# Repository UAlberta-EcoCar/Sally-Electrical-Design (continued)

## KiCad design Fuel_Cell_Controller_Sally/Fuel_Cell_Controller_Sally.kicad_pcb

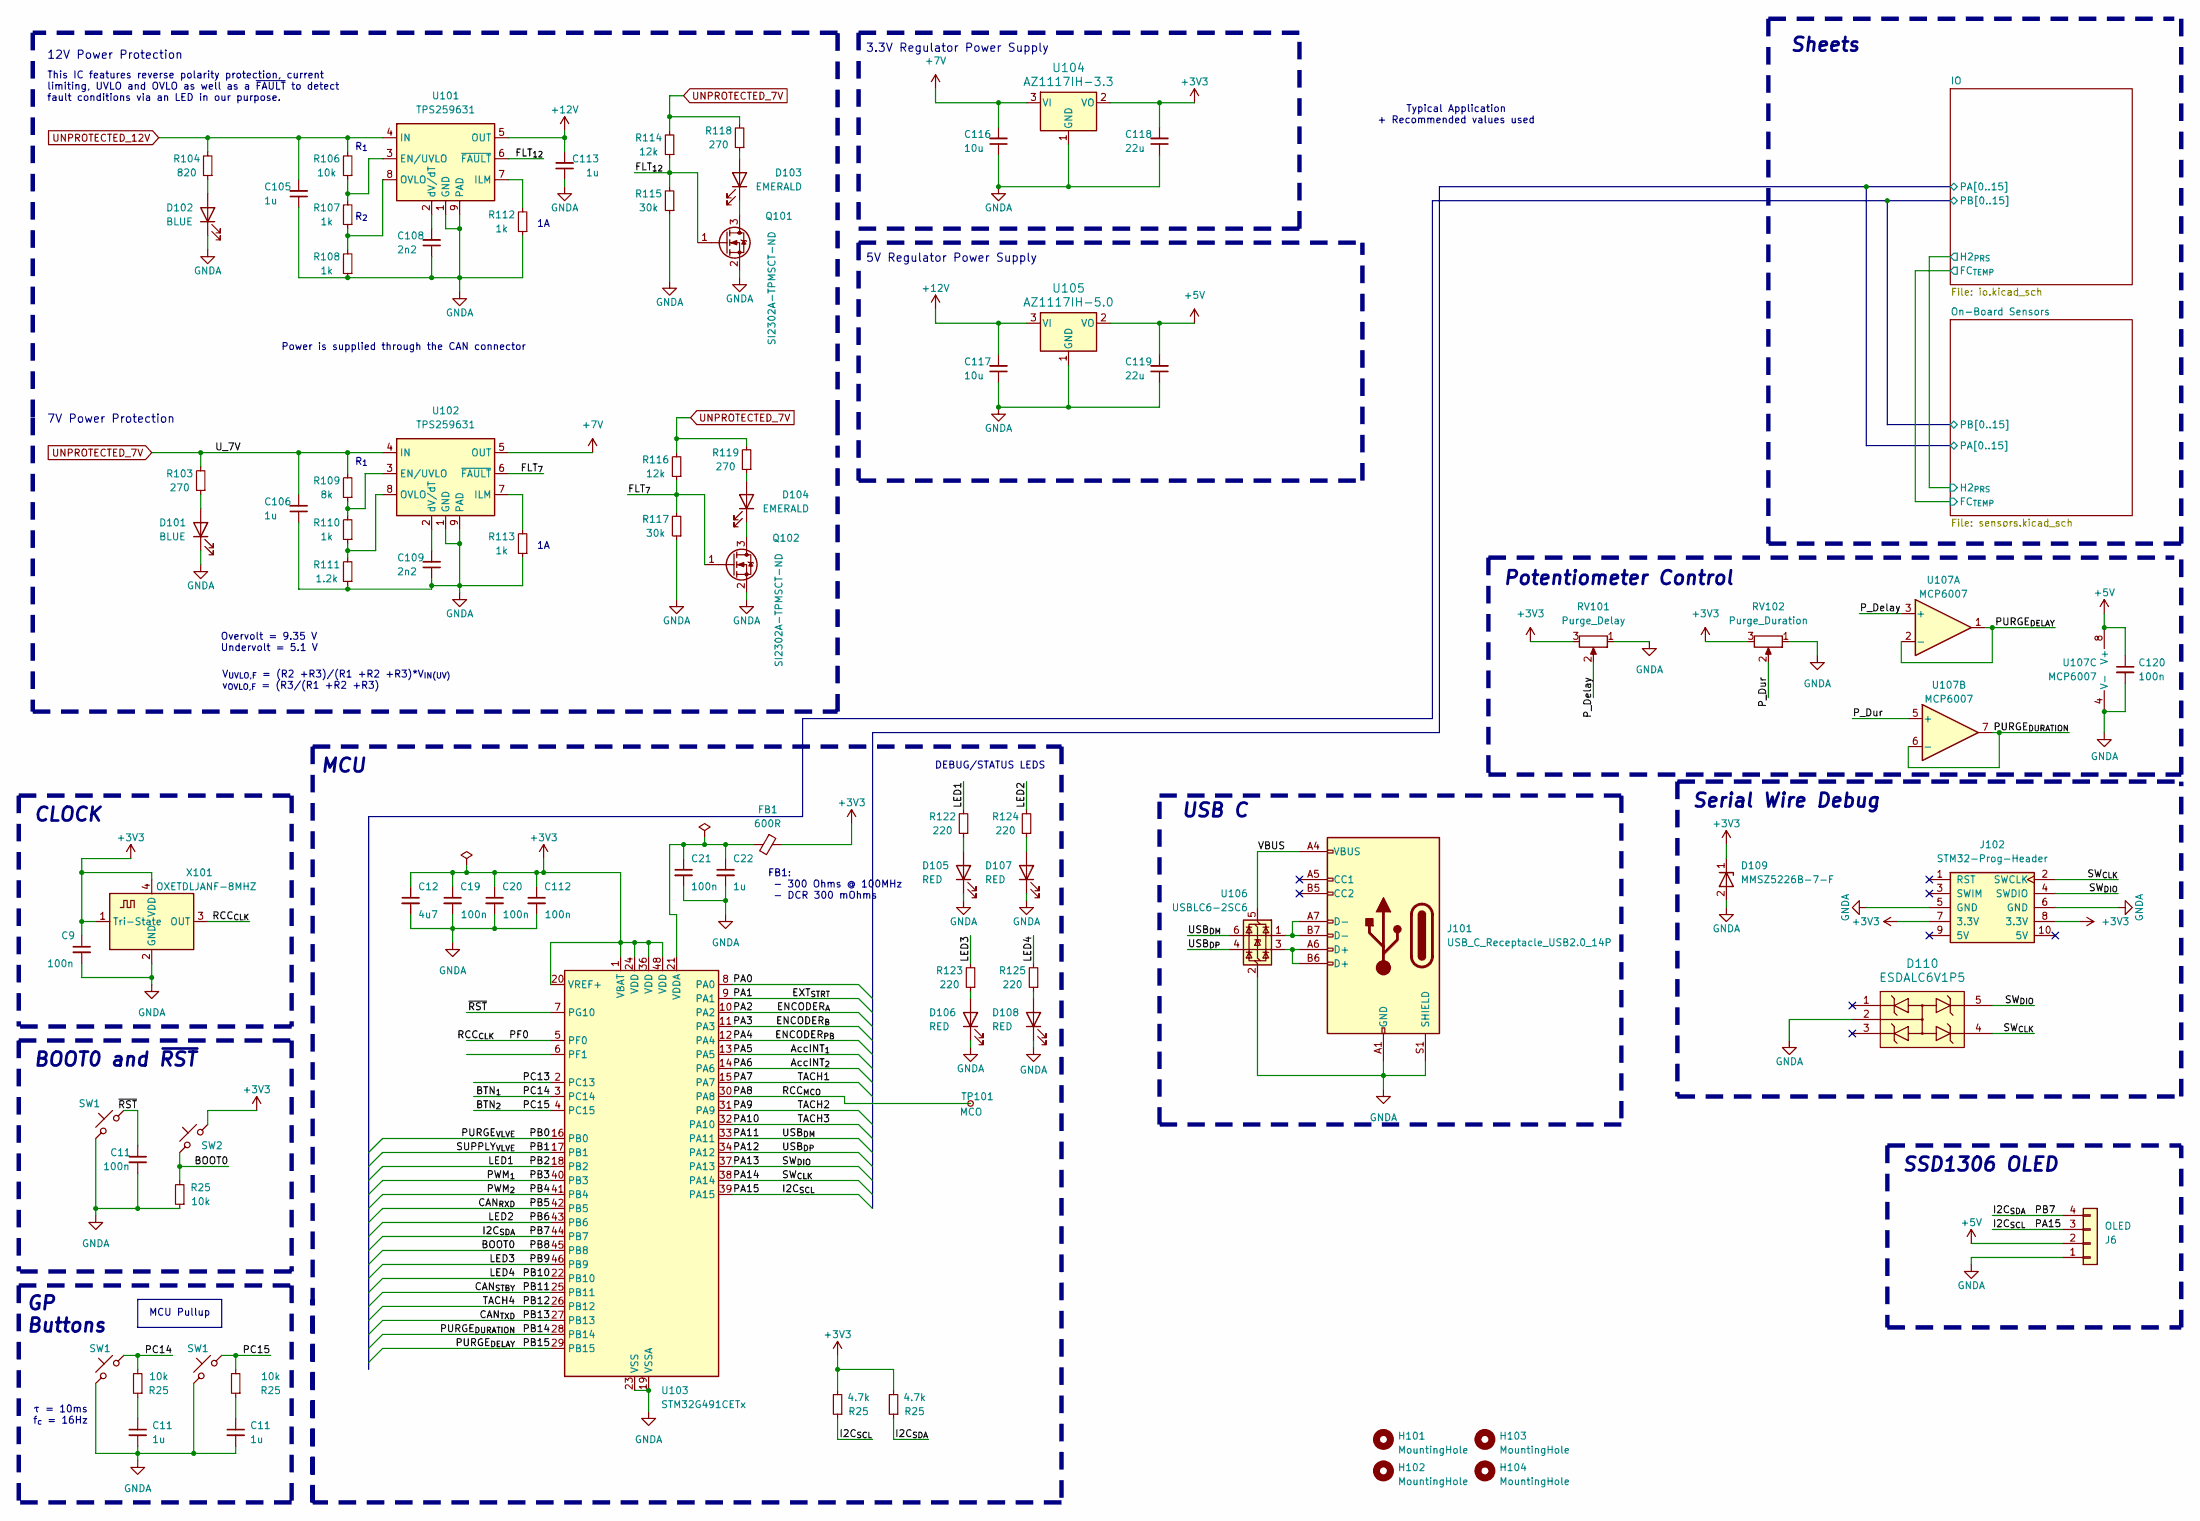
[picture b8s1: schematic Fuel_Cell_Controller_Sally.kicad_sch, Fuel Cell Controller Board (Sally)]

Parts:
C9, C120: 100n; C_0603_1608Metric; Part# C14663
C11: 1u; C_0603_1608Metric; Part# C23630
C12: 4u7; C_0603_1608Metric; Part# C19666
C19, C20, C21, C112: 100n; C_0603_1608Metric; Part# C1525
C22, C105, C106, C113: 1u; C_0603_1608Metric; Part# C15849
C108, C109: 2n2; C_0603_1608Metric; Part# C1604
C116, C117: 10u; C_0603_1608Metric; Part# C15849
C118, C119: 22u; C_0603_1608Metric; Part# C15849
D101, D102: BLUE; LED_0603_1608Metric; Part# C72041
D103, D104: EMERALD; LED_0603_1608Metric; Part# C72043
D105, D106, D107, D108: RED; LED_0603_1608Metric; Part# C72041
D109: MMSZ5226B-7-F; D_SOD_123_M; Part# C155250
D110: ESDALC6V1P5
FB1: 600R; L_0805_2012Metric; Part# C1017
H101, H102, H103, H104: MountingHole; MountingHole_3.5mm
J6: OLED; Display_128x64_096_I2C; Part# N/A
J101: USB_C_Receptacle_USB2.0_14P; USB_C_Receptacle_GCT_USB4105-xx-A_16P_TopMnt_Horizontal
J102: STM32-Prog-Header; IDC-STM32-Prog-Header_2x05_P2.54mm_Vertical
Q101, Q102: SI2302A-TPMSCT-ND; SOT-23-3; Part# SI2302A-TPMSCT-ND
R25: 4.7k; R_0603_1608Metric; Part# C23162
R103, R118, R119: 270; R_0603_1608Metric; Part# C22966
R104: 820; R_0603_1608Metric; Part# C23253
R106: 10k; R_0603_1608Metric; Part# C25804
R107, R108: 1k; R_0603_1608Metric; Part# C3013565
R109: 8k; R_0603_1608Metric; Part# C25950
R110: 1k; R_0603_1608Metric; Part# C25950
R111: 1.2k; R_0603_1608Metric; Part# C25950
R112, R113: 1k; R_0603_1608Metric; Part# C21190
R114, R116: 12k; R_0603_1608Metric; Part# C25803
R115, R117: 30k; R_0603_1608Metric; Part# C25803
R122, R123, R124, R125: 220; R_0603_1608Metric; Part# C22966
RV101: Purge_Delay; Potentiometer_Bourns_PTV09A-1_Single_Vertical
RV102: Purge_Duration; Potentiometer_Bourns_PTV09A-1_Single_Vertical
SW1: SW_PUSH_6mm_H5mm; Part# N/A
SW2: PTS815 SJM 250 SMTR LFS; SW_PUSH_6mm_H5mm; Part# C2689510
TP101: MCO; TestPoint_Pad_D1.0mm; Part# N/A
U101, U102: TPS259631; TI_SO-PowerPAD-8
U103: STM32G491CETx; LQFP-48_7x7mm_P0.5mm
U104: AZ1117IH-3.3; SOT-223-3_TabPin2
U105: AZ1117IH-5.0; SOT-223-3_TabPin2
U106: USBLC6-2SC6; SOT-23-6
U107: MCP6007; SOIC-8_3.9x4.9mm_P1.27mm
X101: OXETDLJANF-8MHZ; Crystal_SMD_3225-4Pin_3.2x2.5mm

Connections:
+3V3: C112.1, C118.2, D109.1, J102.7 (3.3V), J102.8 (3.3V), RV101.3, RV102.3, U103.1 (VBAT), U103.20 (VREF+), U103.24 (VDD), U103.36 (VDD), U103.48 (VDD), U104.2 (VO), X101.1 (Tri-State), X101.4 (VDD); also elsewhere on the board
+5V: C119.2, C120.1, U105.2 (VO), U107.8 (V+); also elsewhere on the board
+7V: C116.2, U102.5 (OUT), U104.3 (VI)
+12V: C113.2, C117.2, U101.5 (OUT), U105.3 (VI); also elsewhere on the board
/BTN_{1}: U103.3 (PC14); also elsewhere on the board
/BTN_{2}: U103.4 (PC15); also elsewhere on the board
/FLT_{7}: Q102.1 (G), R116.1, R117.2, U102.6 (~FAULT)
/FLT_{12}: Q101.1 (G), R114.1, R115.2, U101.6 (~FAULT)
/IO /PA0: U103.8 (PA0)
/IO /PA1: U103.9 (PA1); also elsewhere on the board
/IO /PA2: U103.10 (PA2); also elsewhere on the board
/IO /PA3: U103.11 (PA3); also elsewhere on the board
/IO /PA4: U103.12 (PA4); also elsewhere on the board
/IO /PA5: U103.13 (PA5); also elsewhere on the board
/IO /PA6: U103.14 (PA6); also elsewhere on the board
/IO /PA7: U103.15 (PA7); also elsewhere on the board
/IO /PA8: TP101.1, U103.30 (PA8)
/IO /PA9: U103.31 (PA9); also elsewhere on the board
/IO /PA10: U103.32 (PA10); also elsewhere on the board
/IO /PA11: U103.33 (PA11), U106.6 (I/O1)
/IO /PA12: U103.34 (PA12), U106.4 (I/O2)
/IO /PA13: D110.5, J102.4 (SWDIO), U103.37 (PA13)
/IO /PA14: D110.4, J102.2 (SWCLK), U103.38 (PA14)
/IO /PA15: U103.39 (PA15); also elsewhere on the board
/IO /PB0: U103.16 (PB0); also elsewhere on the board
/IO /PB1: U103.17 (PB1); also elsewhere on the board
/IO /PB2: R122.2, U103.18 (PB2)
/IO /PB3: U103.40 (PB3); also elsewhere on the board
/IO /PB4: U103.41 (PB4); also elsewhere on the board
/IO /PB5: U103.42 (PB5); also elsewhere on the board
/IO /PB6: R124.2, U103.43 (PB6)
/IO /PB7: U103.44 (PB7); also elsewhere on the board
/IO /PB8: U103.45 (PB8); also elsewhere on the board
/IO /PB9: R123.2, U103.46 (PB9)
/IO /PB10: R125.2, U103.22 (PB10)
/IO /PB11: U103.25 (PB11); also elsewhere on the board
/IO /PB12: U103.26 (PB12); also elsewhere on the board
/IO /PB13: U103.27 (PB13); also elsewhere on the board
/IO /PB14: U103.28 (PB14), U107.6 (-), U107.7
/IO /PB15: U103.29 (PB15), U107.1, U107.2 (-)
/PC13: U103.2 (PC13)
/PF0: U103.5 (PF0), X101.3 (OUT)
/P_Delay: RV101.2, U107.3 (+)
/P_Dur: RV102.2, U107.5 (+)
/VBUS: J101.A4 (VBUS), J101.A9 (VBUS), J101.B4 (VBUS), J101.B9 (VBUS), U106.5 (VBUS)
/~RST: U103.7 (PG10); also elsewhere on the board
GNDA: C105.1, C106.1, C108.1, C109.1, C112.2, C113.1, C116.1, C117.1, C118.1, C119.1, C120.2, D101.1 (K), D102.1 (K), D105.1 (K), D106.1 (K), D107.1 (K), D108.1 (K), D109.2, D110.2, J101.A1 (GND), J101.A12 (GND), J101.B1 (GND), J101.B12 (GND), J101.S1 (SHIELD), J102.5 (GND), J102.6 (GND), Q101.2 (S), Q102.2 (S), R108.1, R111.1, R112.1, R113.1, R115.1, R117.1, RV101.1, RV102.1, U101.1 (GND), U101.9 (PAD), U102.1 (GND), U102.9 (PAD), U103.19 (VSSA), U103.23 (VSS), U103.35 (VSS), U103.47 (VSS), U104.1 (GND), U105.1 (GND), U106.2 (GND), U107.4 (V-), X101.2 (GND); also elsewhere on the board
unnamed: D101.2 (A), R103.1
unnamed: D102.2 (A), R104.1
unnamed: D103.2 (A), R118.1
unnamed: D103.1 (K), Q101.3 (D)
unnamed: D104.2 (A), R119.1
unnamed: D104.1 (K), Q102.3 (D)
unnamed: D105.2 (A), R122.1
unnamed: D106.2 (A), R123.1
unnamed: D107.2 (A), R124.1
unnamed: D108.2 (A), R125.1
unnamed: J101.A6 (D+), J101.B6 (D+), U106.3 (I/O2)
unnamed: J101.A7 (D-), J101.B7 (D-), U106.1 (I/O1)
unnamed: R106.1, R107.2, U101.3 (EN/UVLO)
unnamed: R112.2, U101.7 (ILM)
unnamed: R107.1, R108.2, U101.8 (OVLO)
unnamed: C108.2, U101.2 (dV/dT)
unnamed: R109.1, R110.2, U102.3 (EN/UVLO)
unnamed: R113.2, U102.7 (ILM)
unnamed: R110.1, R111.2, U102.8 (OVLO)
unnamed: C109.2, U102.2 (dV/dT)
unnamed 95: U103.21 (VDDA); also elsewhere on the board
UNPROTECTED_7V: C106.2, R103.2, R109.2, R114.2, R116.2, R118.2, R119.2, U102.4 (IN); also elsewhere on the board
UNPROTECTED_12V: C105.2, R104.2, R106.2, U101.4 (IN); also elsewhere on the board

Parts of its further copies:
C101: 100n; C_0603_1608Metric; Part# C14663
C103, C104: 1u; C_0603_1608Metric; Part# C23630
C107: 4u7; C_0603_1608Metric; Part# C19666
C110, C111, C114: 100n; C_0603_1608Metric; Part# C1525
C115: 1u; C_0603_1608Metric; Part# C15849
FB101: 600R; L_0805_2012Metric; Part# C1017
J103: OLED; Display_128x64_096_I2C; Part# N/A
R120, R121: 4.7k; R_0603_1608Metric; Part# C23162
SW102, SW104: SW_PUSH_6mm_H5mm; Part# N/A
SW103: PTS815 SJM 250 SMTR LFS; SW_PUSH_6mm_H5mm; Part# C2689510

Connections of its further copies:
+3V3: C101.1, C107.1, C110.1, C111.1, FB101.1, R120.2, R121.2, SW103.2; also elsewhere on the board
+5V: J103.2; also elsewhere on the board
/BTN_{1}: SW102.2; also elsewhere on the board
/BTN_{2}: SW104.2; also elsewhere on the board
/IO /PA15: J103.3, R120.1; also elsewhere on the board
/IO /PB7: J103.4, R121.1; also elsewhere on the board
/IO /PB8: SW103.1; also elsewhere on the board
GNDA: C101.2, C103.2, C104.2, C107.2, C110.2, C111.2, C114.2, C115.2, J103.1, SW102.1, SW104.1; also elsewhere on the board
unnamed 61: C103.1; also elsewhere on the board
unnamed 62: C104.1; also elsewhere on the board
unnamed 95: C114.1, C115.1, FB101.2; also elsewhere on the board

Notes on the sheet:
MCU
R_{1}
FB1: - 300 Ohms @ 100MHz - DCR 300 mOhms
Sheets
12V Power Protection
Power is supplied through the CAN connector
Potentiometer Control
5V Regulator Power Supply
DEBUG/STATUS LEDS
CLOCK
Typical Application + Recommended values used
GP Buttons
SSD1306 OLED
This IC features reverse polarity protection, current limiting, UVLO and OVLO as well as a ~{FAULT} to detect fault conditions via an LED in our purpose.
7V Power Protection
R_{2}
3.3V Regulator Power Supply
USB C
Serial Wire Debug
BOOT0 and ~{RST}
Overvolt = 9.35 V Undervolt = 5.1 V
MCU Pullup
τ = 10ms f_{c} = 16Hz
V_{UVLO,F} = (R2 +R3)/(R1 +R2 +R3)*V_{IN(UV)} v_{OVLO,F} = (R3/(R1 +R2 +R3)

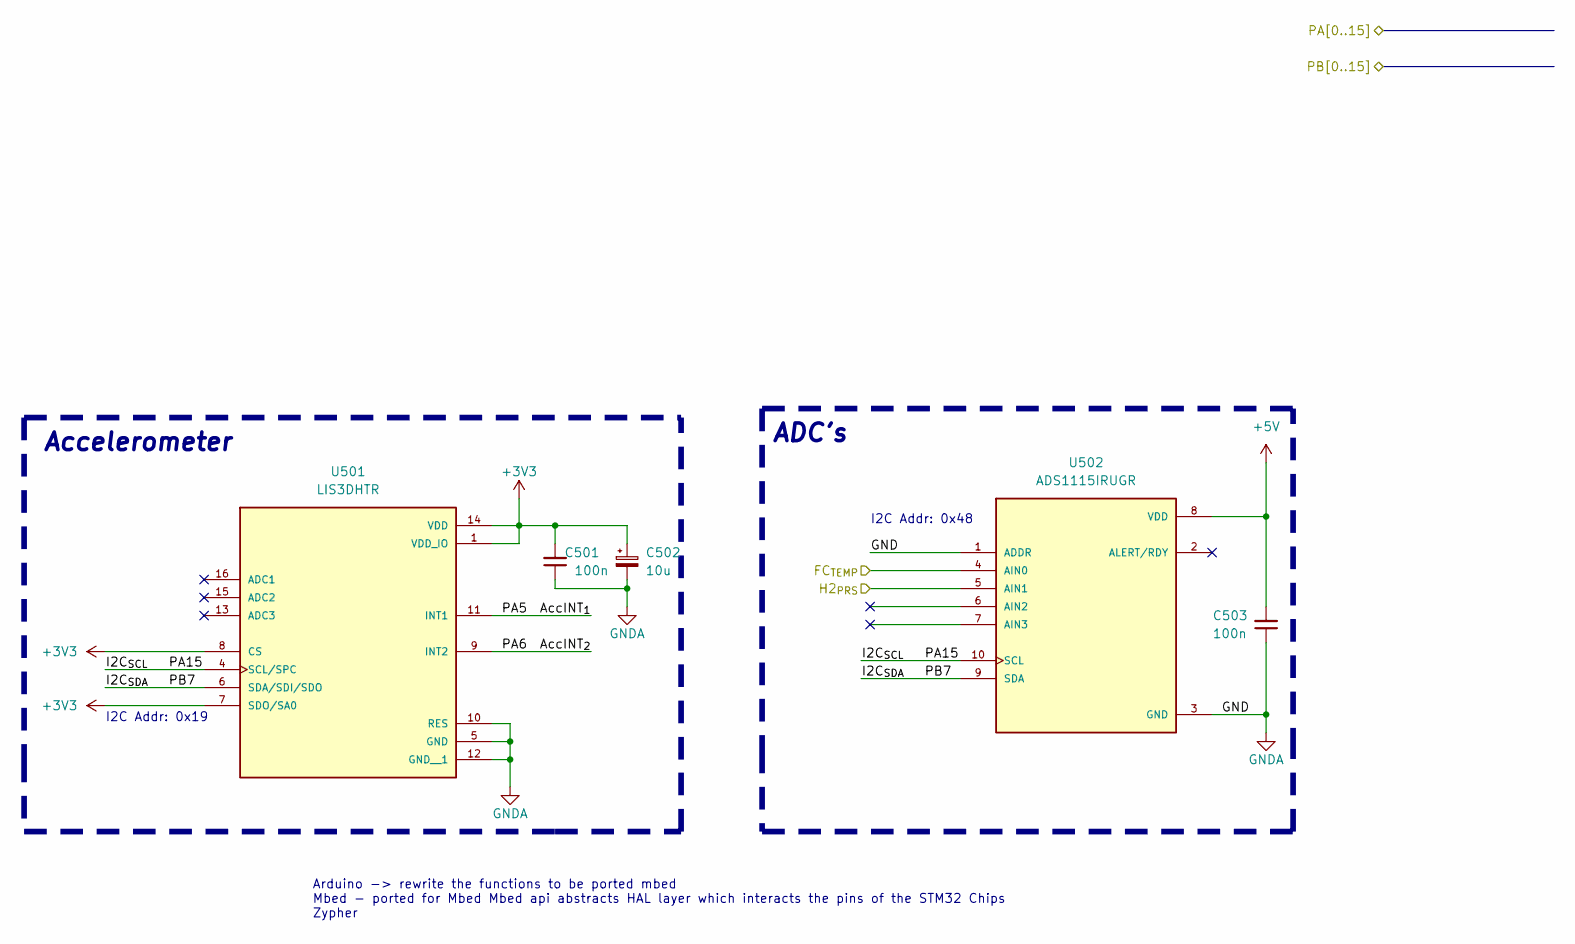
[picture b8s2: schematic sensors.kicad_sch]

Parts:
C501, C503: 100n; C_0603_1608Metric; Part# C14663
C502: 10u; CP_Elec_3x5.3
U501: LIS3DHTR; XDCR_LIS3DHTR
U502: ADS1115IRUGR; IC_ADS1115IRUGR

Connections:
+3V3: C501.2, C502.1, U501.1 (VDD_IO), U501.7 (SDO/SA0), U501.8 (CS), U501.14 (VDD); also elsewhere on the board
+5V: C503.2, U502.8 (VDD); also elsewhere on the board
/IO /FC_{TEMP}: U502.4 (AIN0); also elsewhere on the board
/IO /H2_{PRS}: U502.5 (AIN1); also elsewhere on the board
/IO /PA5: U501.11 (INT1); also elsewhere on the board
/IO /PA6: U501.9 (INT2); also elsewhere on the board
/IO /PA15: U501.4 (SCL/SPC), U502.10 (SCL); also elsewhere on the board
/IO /PB7: U501.6 (SDA/SDI/SDO), U502.9 (SDA); also elsewhere on the board
GNDA: C501.1, C502.2, C503.1, U501.5 (GND), U501.10 (RES), U501.12 (GND__1), U502.1 (ADDR), U502.3 (GND); also elsewhere on the board

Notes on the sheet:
I2C Addr: 0x48
Arduino -> rewrite the functions to be ported mbed Mbed - ported for Mbed Mbed api abstracts HAL layer which interacts the pins of the STM32 Chips Zypher
ADC's
I2C Addr: 0x19
Accelerometer

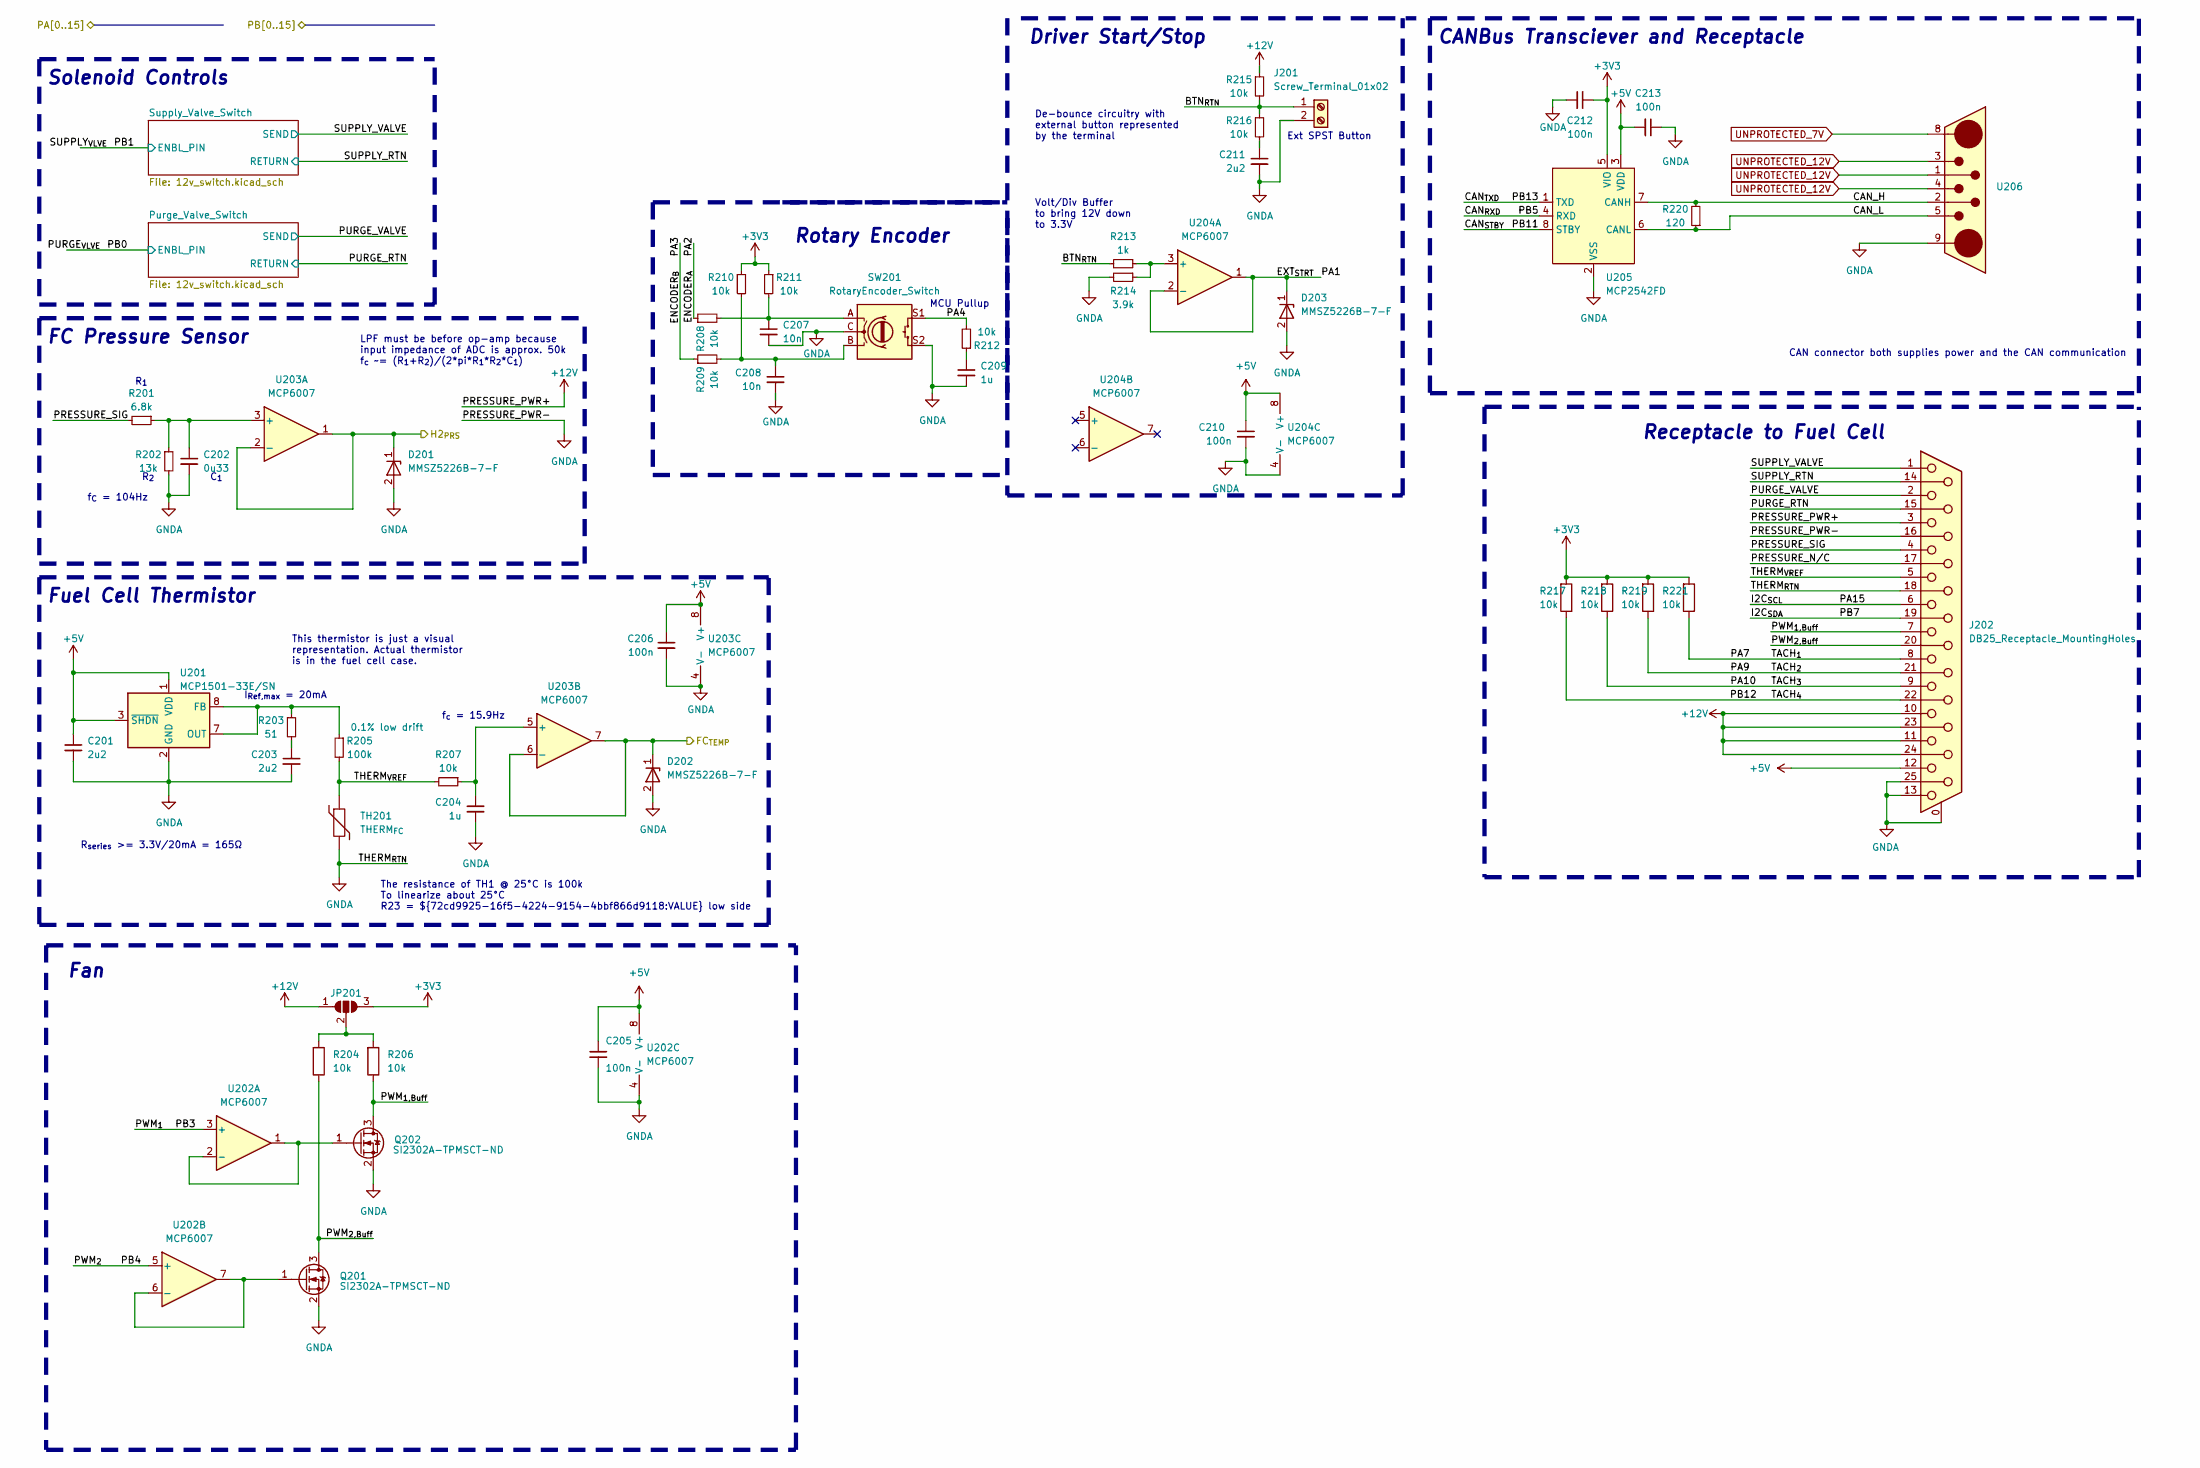
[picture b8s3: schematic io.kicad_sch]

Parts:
C201, C203, C211: 2u2; C_0603_1608Metric; Part# C23630
C202: 0u33; C_0603_1608Metric; Part# C1615
C204: 1u; C_0603_1608Metric; Part# C15849
C205: 100n; C_0603_1608Metric; Part# C77049
C206, C210, C212, C213: 100n; C_0603_1608Metric; Part# C14663
C207, C208: 10n; C_0603_1608Metric; Part# C23630
C209: 1u; C_0603_1608Metric; Part# C23630
D201, D202, D203: MMSZ5226B-7-F; D_SOD_123_M; Part# C155250
J201: Screw_Terminal_01x02; TerminalBlock_Phoenix_MKDS-1,5-2-5.08_1x02_P5.08mm_Horizont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; Part# 277-1247-ND
J202: DB25_Receptacle_MountingHoles; DSUB-25_Female_Horizontal_P2.77x2.84mm_EdgePinOffset9.90mm_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
JP201: SolderJumper_3_Open; SolderJumper-3_P1.3mm_Open_RoundedPad1.0x1.5mm_NumberLabels
Q201, Q202: SI2302A-TPMSCT-ND; SOT-23-3; Part# SI2302A-TPMSCT-ND
R201: 6.8k; R_0603_1608Metric; Part# C23212
R202: 13k; R_0603_1608Metric; Part# C22797
R203: 51; R_0603_1608Metric; Part# C23197
R204, R206, R217, R218, R219, R221: 10k; R_0603_1608Metric; LCSC # C25804
R205: 100k; R_0603_1608Metric; Part# C25803
R207, R208, R209, R210, R211, R212, R215, R216: 10k; R_0603_1608Metric; Part# C25804
R213: 1k; R_0603_1608Metric; Part# C4190
R214: 3.9k; R_0603_1608Metric; Part# C23253
R220: 120; R_0603_1608Metric; Part# C22787
SW201: RotaryEncoder_Switch; RotaryEncoder_Bourns_Vertical_PEC12R-3x17F-Sxxxx
TH201: THERM_{FC}; Part# N/A
U201: MCP1501-33E/SN; SOIC-8_3.9x4.9mm_P1.27mm; Part# MCP1501-33E/SN-ND
U202, U203, U204: MCP6007; SOIC-8_3.9x4.9mm_P1.27mm
U205: MCP2542FD; SOIC-8_3.9x4.9mm_P1.27mm
U206: DB7W2-Male

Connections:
+3V3: C212.1, JP201.3 (B), R210.1, R211.1, R217.2, R218.2, R219.2, R221.2, U205.5 (VIO); also elsewhere on the board
+5V: C201.1, C205.1, C206.1, C210.1, C213.2, J202.12, U201.1 (VDD), U201.3 (~SHDN), U202.8 (V+), U203.8 (V+), U204.8 (V+), U205.3 (VDD); also elsewhere on the board
+12V: J202.1, J202.2, J202.3, J202.10, J202.11, J202.23, J202.24, JP201.1 (A), R215.1; also elsewhere on the board
/IO /BTN_{RTN}: J201.1, R213.2, R215.2, R216.1
/IO /CAN_H: R220.2, U205.7 (CANH), U206.2
/IO /CAN_L: R220.1, U205.6 (CANL), U206.5
/IO /FC_{TEMP}: D202.1, U203.6 (-), U203.7; also elsewhere on the board
/IO /H2_{PRS}: D201.1, U203.1, U203.2 (-); also elsewhere on the board
/IO /PA1: D203.1, U204.1, U204.2 (-); also elsewhere on the board
/IO /PA2: R208.1; also elsewhere on the board
/IO /PA3: R209.1; also elsewhere on the board
/IO /PA4: R212.2, SW201.S1; also elsewhere on the board
/IO /PA7: J202.8, R221.1; also elsewhere on the board
/IO /PA9: J202.21, R219.1; also elsewhere on the board
/IO /PA10: J202.9, R218.1; also elsewhere on the board
/IO /PA15: J202.6; also elsewhere on the board
/IO /PB3: U202.3 (+); also elsewhere on the board
/IO /PB4: U202.5 (+); also elsewhere on the board
/IO /PB5: U205.4 (RXD); also elsewhere on the board
/IO /PB7: J202.19; also elsewhere on the board
/IO /PB11: U205.8 (STBY); also elsewhere on the board
/IO /PB12: J202.22, R217.1; also elsewhere on the board
/IO /PB13: U205.1 (TXD); also elsewhere on the board
/IO /PRESSURE_N/C: J202.17
/IO /PRESSURE_SIG: J202.4, R201.2
/IO /PURGE_RTN: J202.15; also elsewhere on the board
/IO /PWM_{1,Buff}: J202.7, Q202.3 (D), R206.1
/IO /PWM_{2,Buff}: J202.20, Q201.3 (D), R204.1
/IO /SUPPLY_RTN: J202.14; also elsewhere on the board
/IO /THERM_{VREF}: J202.5, R205.2, R207.2, TH201.1
GNDA: C201.2, C202.2, C203.2, C204.2, C205.2, C206.2, C207.2, C208.2, C209.2, C210.2, C211.2, C212.2, C213.1, D201.2, D202.2, D203.2, J201.2, J202.0 (PAD), J202.13, J202.16, J202.18, J202.25, Q201.2 (S), Q202.2 (S), R202.2, R214.2, SW201.C, SW201.S2, TH201.2, U201.2 (GND), U201.4 (GND), U201.5 (GND), U201.6 (GND), U202.4 (V-), U203.4 (V-), U204.4 (V-), U205.2 (VSS), U206.9; also elsewhere on the board
unnamed: C203.1, R203.2
unnamed: C207.1, R208.2, R211.2, SW201.A
unnamed: C208.1, R209.2, R210.2, SW201.B
unnamed: C209.1, R212.1
unnamed: C211.1, R216.2
unnamed: JP201.2 (C), R204.2, R206.2
unnamed: Q201.1 (G), U202.6 (-), U202.7
unnamed: Q202.1 (G), U202.1, U202.2 (-)
unnamed: R203.1, R205.1, U201.7 (OUT), U201.8 (FB)
unnamed: C202.1, R201.1, R202.1, U203.3 (+)
unnamed: C204.1, R207.1, U203.5 (+)
unnamed: R213.1, R214.1, U204.3 (+)
UNPROTECTED_7V: U206.8; also elsewhere on the board
UNPROTECTED_12V: U206.1, U206.3, U206.4; also elsewhere on the board

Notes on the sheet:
Ext SPST Button
f_{c} = 15.9Hz
Volt/Div Buffer to bring 12V down to 3.3V
This thermistor is just a visual representation. Actual thermistor is in the fuel cell case.
FC Pressure Sensor
MCU Pullup
Rotary Encoder
CANBus Transciever and Receptacle
I_{Ref,max} = 20mA
The resistance of TH1 @ 25°C is 100k To linearize about 25°C R23 = ${72cd9925-16f5-4224-9154-4bbf866d9118:VALUE} low side
De-bounce circuitry with external button represented by the terminal
LPF must be before op-amp because input impedance of ADC is approx. 50k f_{c} ~= (R_{1}+R_{2})/(2*pi*R_{1}*R_{2}*C_{1})
Fan
C_{1}
R_{1}
R_{series} >= 3.3V/20mA = 165Ω
Receptacle to Fuel Cell
CAN connector both supplies power and the CAN communication
f_{C} = 104Hz
Solenoid Controls
Driver Start/Stop
Fuel Cell Thermistor
R_{2}

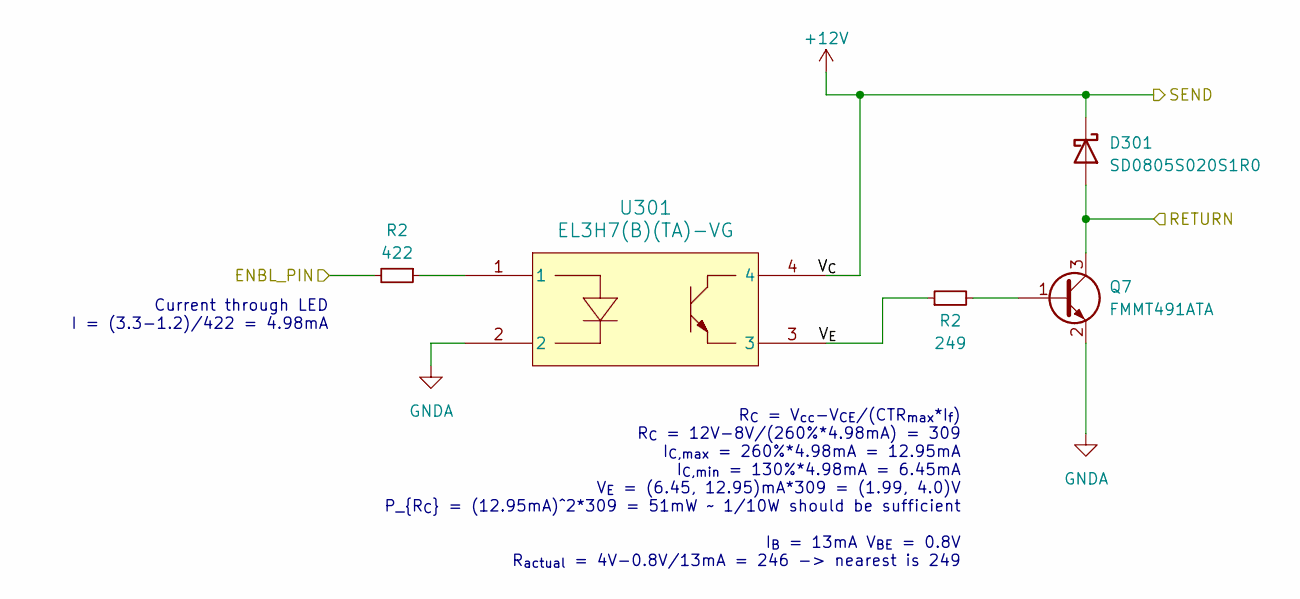
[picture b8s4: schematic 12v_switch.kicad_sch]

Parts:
D301: SD0805S020S1R0; D_0805_2012Metric_Pad1.15x1.40mm_HandSolder; Part# 478-7800-1-ND
Q7: FMMT491ATA; SOT-23-3; Part# C110504
R2: 422; R_0603_1608Metric; Part# C101033
U301: EL3H7(B)(TA)-VG; SOIC_BTA-VG_EVS

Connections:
+12V: D301.1 (K), U301.4; also elsewhere on the board
/IO /SUPPLY_RTN: D301.2 (A); also elsewhere on the board
/IO /Supply_Valve_Switch/V_{E}: U301.3; also elsewhere on the board
GNDA: U301.2; also elsewhere on the board
unnamed 85: U301.1; also elsewhere on the board

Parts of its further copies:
D401: SD0805S020S1R0; D_0805_2012Metric_Pad1.15x1.40mm_HandSolder; Part# 478-7800-1-ND
Q301, Q401: FMMT491ATA; SOT-23-3; Part# C110504
R301, R401: 422; R_0603_1608Metric; Part# C101033
U401: EL3H7(B)(TA)-VG; SOIC_BTA-VG_EVS

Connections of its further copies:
+12V: D401.1 (K), U401.4; also elsewhere on the board
/IO /PB0: R401.2; also elsewhere on the board
/IO /PB1: R301.2; also elsewhere on the board
/IO /PURGE_RTN: D401.2 (A), Q401.3 (C); also elsewhere on the board
/IO /Purge_Valve_Switch/V_{E}: U401.3; also elsewhere on the board
/IO /SUPPLY_RTN: Q301.3 (C); also elsewhere on the board
GNDA: Q301.2 (E), Q401.2 (E), U401.2; also elsewhere on the board
unnamed 83: Q301.1 (B); also elsewhere on the board
unnamed 84: Q401.1 (B); also elsewhere on the board
unnamed 85: R301.1; also elsewhere on the board
unnamed: R401.1, U401.1

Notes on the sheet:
R_{C} = V_{cc}-V_{CE}/(CTR_{max}*I_{f}) R_{C} = 12V-8V/(260%*4.98mA) = 309 I_{C,max} = 260%*4.98mA = 12.95mA I_{C,min} = 130%*4.98mA = 6.45mA V_{E} = (6.45, 12.95)mA*309 = (1.99, 4.0)V P_{R_{C}} = (12.95mA)^2*309 = 51mW ~ 1/10W should be sufficient I_{B} = 13mA V_{BE} = 0.8V R_{actual} = 4V-0.8V/13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
Current through LED I = (3.3-1.2)/422 = 4.98mA

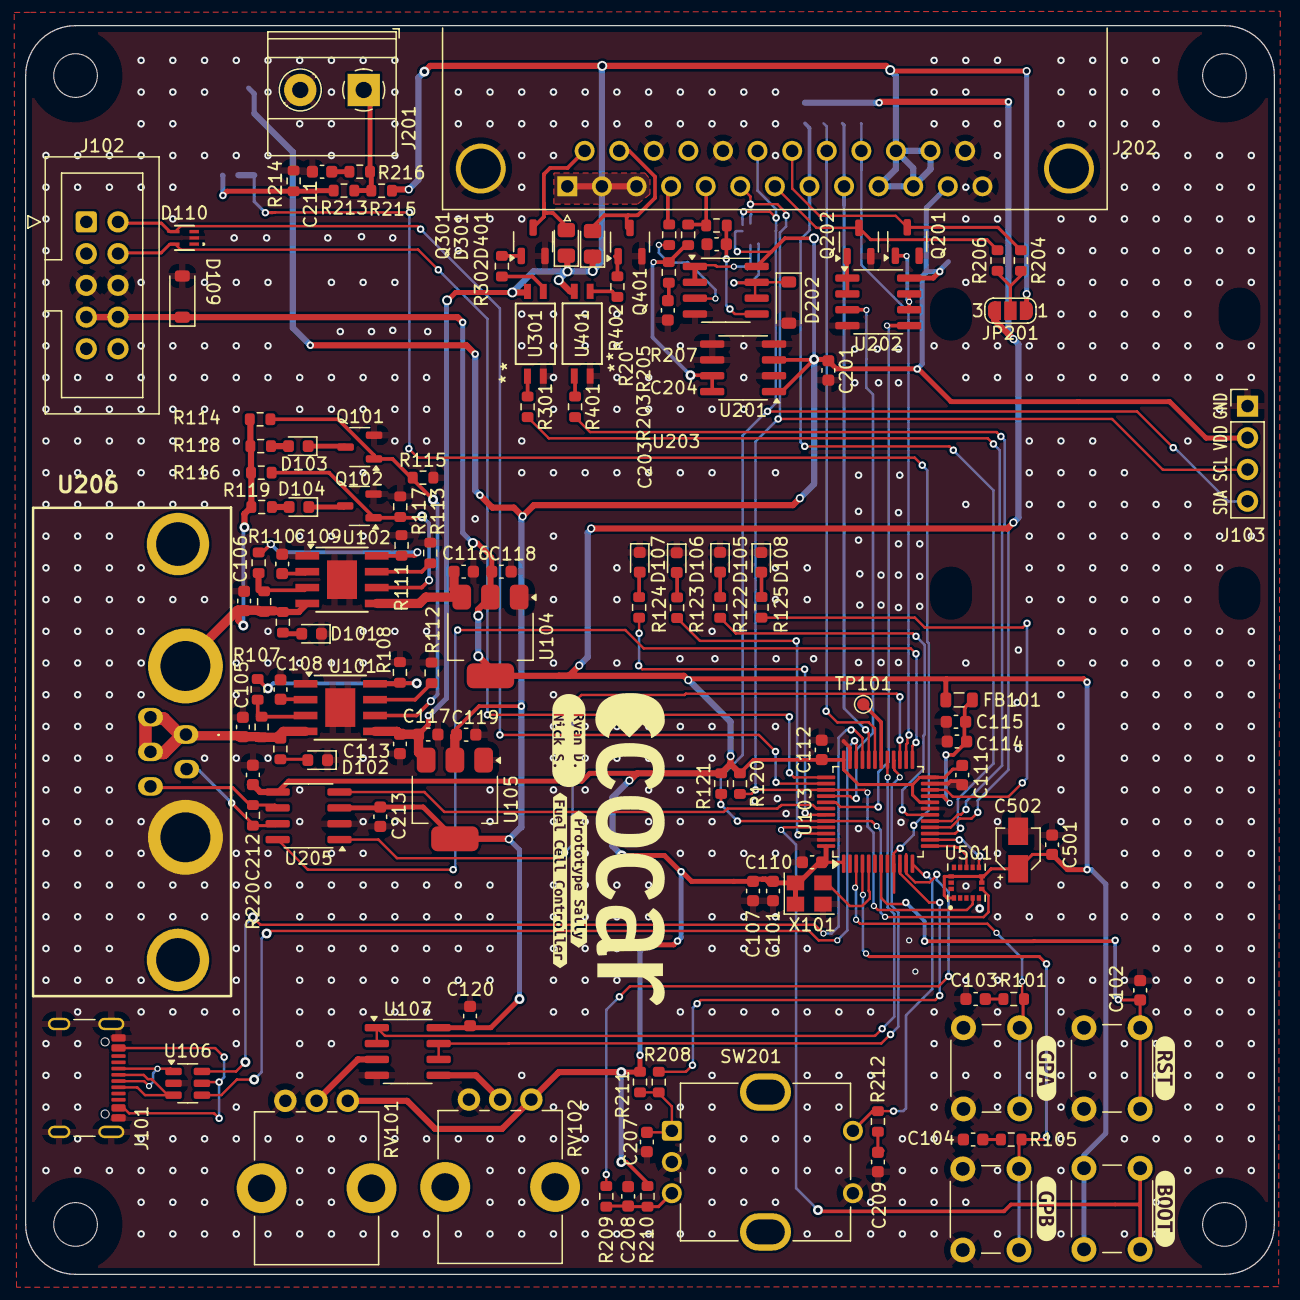
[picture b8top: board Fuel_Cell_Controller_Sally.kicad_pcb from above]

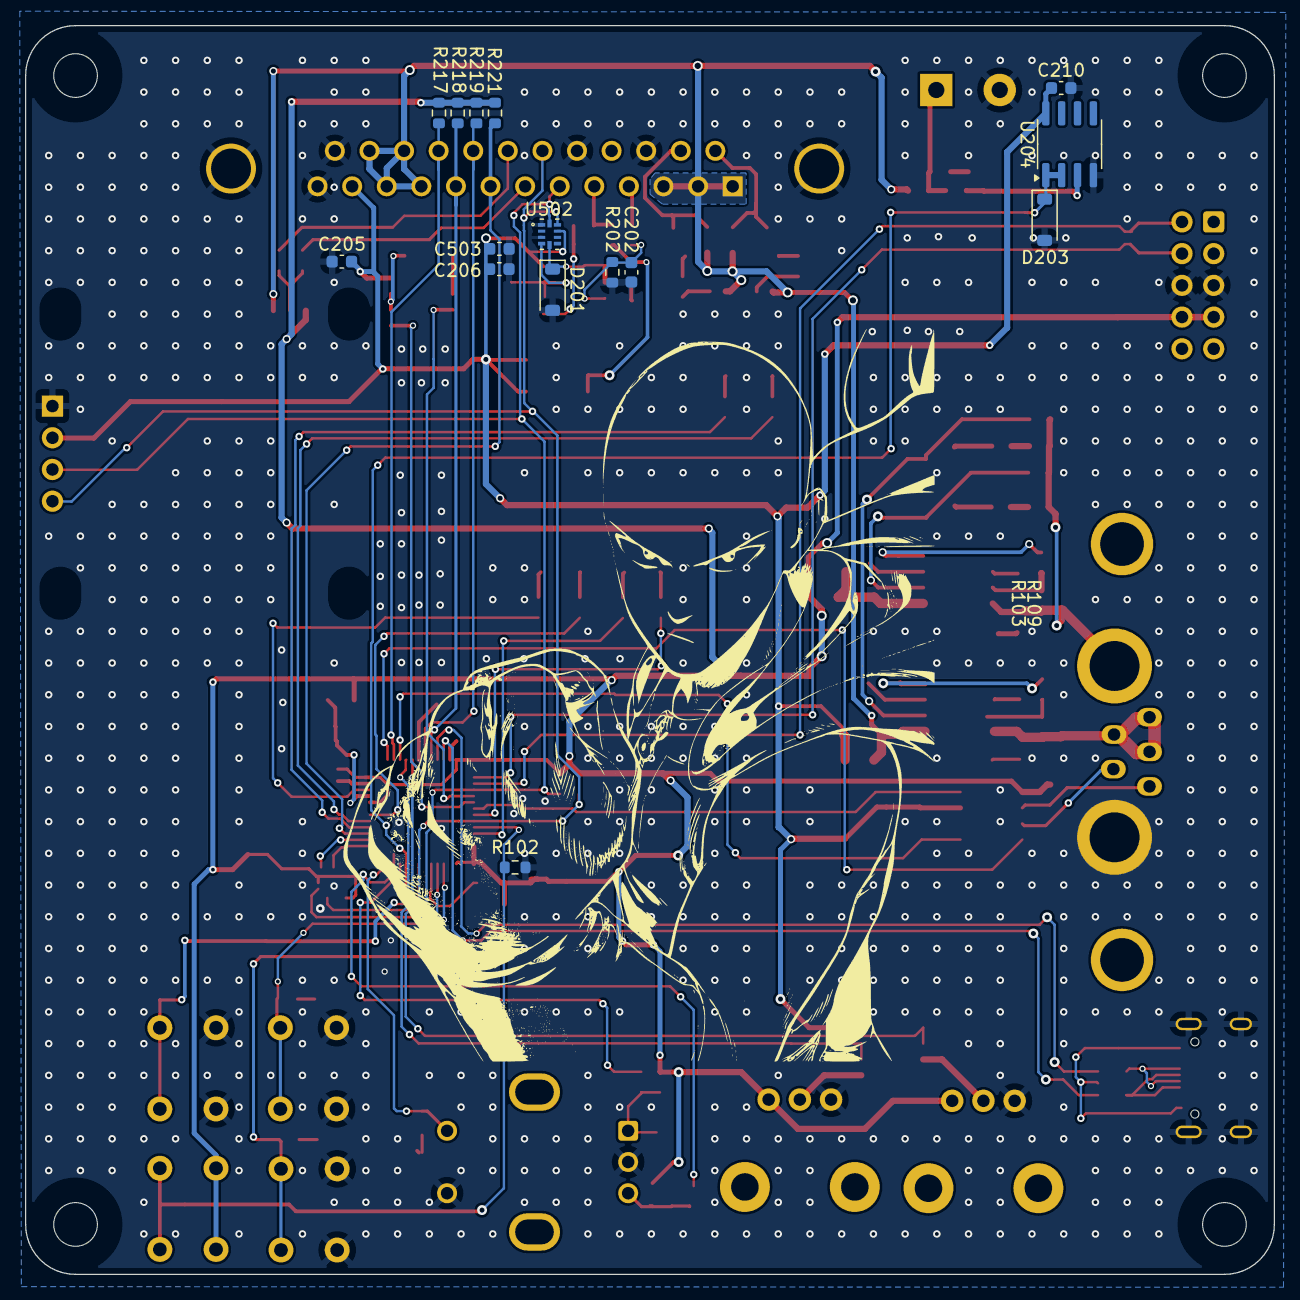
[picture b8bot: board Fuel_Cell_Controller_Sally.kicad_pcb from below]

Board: 2 copper layers, 100.0 x 100.0 mm, 152 parts (15 on the bottom side), 99 nets.

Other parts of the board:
C102: 100n; C_0603_1608Metric
Display 128x64 0.96" I2C: Display_128x64; Display_128x64_096_I2C
R101, R102, R105: 10k; R_0603_1608Metric
R302, R402: 249; R_0603_1608Metric
SW101: PTS815 SJM 250 SMTR LFS; SW_PUSH_6mm_H5mm
kibuzzard-677DE6B4: G***; kibuzzard-677DE6B4
kibuzzard-677DE6B8: G***; kibuzzard-677DE6B8
kibuzzard-677DE645: G***; kibuzzard-677DE645
kibuzzard-677DE649: G***; kibuzzard-677DE649
kibuzzard-677F045B: G***; kibuzzard-677F045B
kibuzzard-6768F859: G***; kibuzzard-6768F859
kibuzzard-6768F875: G***; kibuzzard-6768F875

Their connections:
/BTN_{1}: R101.2; also elsewhere on the board
/BTN_{2}: R105.2; also elsewhere on the board
/IO /PB8: R102.2; also elsewhere on the board
/IO /Purge_Valve_Switch/V_{E}: R402.1; also elsewhere on the board
/IO /Supply_Valve_Switch/V_{E}: R302.1; also elsewhere on the board
/~RST: C102.1, SW101.2; also elsewhere on the board
GNDA: C102.2, R102.1, SW101.1; also elsewhere on the board
unnamed 61: R101.1; also elsewhere on the board
unnamed 62: R105.1; also elsewhere on the board
unnamed 83: R302.2; also elsewhere on the board
unnamed 84: R402.2; also elsewhere on the board
